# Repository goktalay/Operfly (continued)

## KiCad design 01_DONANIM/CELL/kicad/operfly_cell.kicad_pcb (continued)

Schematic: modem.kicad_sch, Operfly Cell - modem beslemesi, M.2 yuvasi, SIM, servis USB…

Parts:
C24, C25: 10u 50V; C_1206_3216Metric
C26: 100n 50V; C_0603_1608Metric
C27: 15n; C_0402_1005Metric
C28, C38, C39: 220p; C_0402_1005Metric
C29: 100n 25V; C_0603_1608Metric
C30, C31: 47u 16V; C_1210_3225Metric
C32, C35, C36, C45, C49, C53, C54: 100n; C_0402_1005Metric
C33, C34: 220u 6V3 polimer; CP_EIA-7343-31_Kemet-D
C37: 6n8; C_0402_1005Metric
C40, C41: 68p; C_0402_1005Metric
C42: 15p; C_0402_1005Metric
C43: 9p1; C_0402_1005Metric
C44: 4p7; C_0402_1005Metric
C46, C47, C48, C50, C51, C52: 10p; C_0402_1005Metric
C55: 1u 25V; C_0603_1608Metric
D6: PDS760 (60 V, 7 A); D_PowerDI-5
D7: SMAJ5.0A; D_SMA
D8: LED mavi (radyo acik); LED_0603_1608Metric
D9, D10: TPD4E05U06DQA; USON-10_2.5x1.0mm_P0.5mm
D11: USBLC6-2P6; SOT-666
J2: M.2 Key B (5G modem, 3052); TE_M.2_B_2x38-1MP_P0.5mm
J3: nano-SIM 1; nanoSIM_GCT_SIM8060-6-0-14-00
J4: nano-SIM 2; nanoSIM_GCT_SIM8060-6-0-14-00
J5: USB Type-C (servis); USB_C_Receptacle_GCT_USB4105-xx-A_16P_TopMnt_Horizontal
L2: 10u XAL7070-103; L_Coilcraft_XAL7070-XXX
Q1, Q2: 2N7002; SOT-23
R13: 294k 1%; R_0402_1005Metric
R14: 43k2 1%; R_0402_1005Metric
R15: 243k 1%; R_0402_1005Metric
R16: 26k7; R_0402_1005Metric
R17: 38k3 1%; R_0402_1005Metric
R18: 10k2 1%; R_0402_1005Metric
R19, R20: 10k 1%; R_0402_1005Metric
R21, R22, R23, R43, R44: 100k; R_0402_1005Metric
R24, R25: 10k; R_0402_1005Metric
R26: 330R; R_0402_1005Metric
R27, R28, R29, R31, R32, R33: 22R; R_0402_1005Metric
R30, R34: 15k; R_0402_1005Metric
R35, R36, R37, R38, R39, R40: 0R; R_0402_1005Metric
R41, R42: 15k DNP; R_0402_1005Metric; not fitted
R45, R46: 5k1 1%; R_0402_1005Metric
TP4: +3V8_MODEM; TestPoint_Pad_D1.0mm
TP5: MODEM_RESET_N; TestPoint_Pad_D1.0mm
TP6: MODEM_ON; TestPoint_Pad_D1.0mm
U7: TPS54560BDDAR; Texas_R-PDSO-G8_EP2.95x4.9mm_Mask2.4x3.1mm_ThermalVias
U8: FSUSB42MUX; MSOP-10_3x3mm_P0.5mm

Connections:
+3V3: C53.1, R24.1, R25.1, U8.1 (VCC); also elsewhere on the board
+3V8_MODEM: C30.1, C31.1, C33.1, C34.1, C35.1, C36.1, C37.1, C38.1, C39.1, C40.1, C41.1, C42.1, C43.1, C44.1, D7.1 (A1), J2.2 (3.3V), J2.4 (3.3V), J2.70 (3.3V), J2.72 (3.3V), J2.74 (3.3V), L2.2, R17.1, R19.1, R26.1, TP4.1; also elsewhere on the board
+12V: C24.1, C25.1, C26.1, R13.1, U7.2 (VIN); also elsewhere on the board
GND: C24.2, C25.2, C26.2, C27.2, C28.2, C30.2, C31.2, C32.2, C33.2, C34.2, C35.2, C36.2, C37.2, C38.2, C39.2, C40.2, C41.2, C42.2, C43.2, C44.2, C45.2, C46.2, C47.2, C48.2, C49.2, C50.2, C51.2, C52.2, C53.2, C54.2, C55.2, D6.2 (A), D7.2 (A2), D9.3 (GND), D9.8 (GND), D10.3 (GND), D10.8 (GND), D11.2 (GND), J2.3 (GND), J2.5 (GND), J2.11 (GND), J2.27 (GND), J2.33 (GND), J2.39 (GND), J2.45 (GND), J2.51 (GND), J2.57 (GND), J2.71 (GND), J2.73 (GND), J3.5 (GND), J3.SH, J4.5 (GND), J4.SH, J5.A1 (GND), J5.A12 (GND), J5.B1 (GND), J5.B12 (GND), J5.SH (SHIELD), Q1.2 (S), Q2.2 (S), R14.2, R15.2, R18.2, R20.2, R21.2, R22.2, R23.2, R41.2, R42.2, R44.2, R45.2, R46.2, U7.7 (GND), U7.9 (GND), U8.5 (GND), U8.10 (~OE); also elsewhere on the board
MCU_USB_DM: R42.1, U8.6 (HSD1-); also elsewhere on the board
MCU_USB_DP: R41.1, U8.7 (HSD1+); also elsewhere on the board
MDM_BOOT: C29.1, U7.1 (BOOT)
MDM_COMP: C28.1, R16.1, U7.6 (COMP)
MDM_COMP_RC: C27.1, R16.2
MDM_EN: Q1.3 (D), R13.2, R14.1, U7.3 (EN)
MDM_FB: R17.2, R18.1, U7.5 (FB)
MDM_RT: R15.1, U7.4 (RT/CLK)
MDM_SW: C29.2, D6.1 (K), L2.1, U7.8 (SW)
MODEM_LED_A: D8.2 (A), R26.2
MODEM_LED_N: D8.1 (K), J2.10 (GPIO_9/DAS/~DSS/~LED1)
MODEM_ON: J2.6 (~FULL_CARD_POWER_OFF), R23.1, TP6.1; also elsewhere on the board
MODEM_PWR_OFF: Q1.1 (G), R21.1; also elsewhere on the board
MODEM_RESET_N: J2.67 (~RESET), Q2.3 (D), TP5.1
MODEM_RF_EN: J2.8 (~W_DISABLE1), R24.2; also elsewhere on the board
MODEM_RST: Q2.1 (G), R22.1; also elsewhere on the board
MODEM_USB_DM: R40.2, U8.4 (D-)
MODEM_USB_DM_M: J2.9 (USB_D-), R40.1
MODEM_USB_DP: R39.2, U8.3 (D+)
MODEM_USB_DP_M: J2.7 (USB_D+), R39.1
MODEM_VSENS: C32.1, R19.2, R20.1; also elsewhere on the board
MODEM_WAKE_N: J2.23 (GPIO_11), R25.2; also elsewhere on the board
PCIE_CLKREQ_N: J2.52 (~CLKREQ); also elsewhere on the board
PCIE_CLK_N: J2.53 (REFCLKn); also elsewhere on the board
PCIE_CLK_P: J2.55 (REFCLKp); also elsewhere on the board
PCIE_MRX_N: J2.47 (PETn0/SATA-A-); also elsewhere on the board
PCIE_MRX_P: J2.49 (PETp0/SATA-A+); also elsewhere on the board
PCIE_MTX_N: J2.41 (PERn0/SATA-B+); also elsewhere on the board
PCIE_MTX_P: J2.43 (PERp0/SATA-B-); also elsewhere on the board
PCIE_RST_N: J2.50 (~PERST); also elsewhere on the board
PCIE_WAKE_N: J2.54 (~PEWAKE); also elsewhere on the board
SVC_USB_DM: D11.3 (I/O2), D11.4 (I/O2), J5.A7 (D-), J5.B7 (D-), U8.8 (HSD2-)
SVC_USB_DP: D11.1 (I/O1), D11.6 (I/O1), J5.A6 (D+), J5.B6 (D+), U8.9 (HSD2+)
USB_CC1: J5.A5 (CC1), R45.1
USB_CC2: J5.B5 (CC2), R46.1
USB_SEL: C54.1, R43.2, R44.1, U8.2 (SEL); also elsewhere on the board
USB_VBUS: C55.1, D11.5 (VBUS), J5.A4 (VBUS), J5.A9 (VBUS), J5.B4 (VBUS), J5.B9 (VBUS), R43.1
USIM1_CLK: J2.32 (UIM-CLK), R28.1
USIM1_CLK_K: C47.1, D9.4 (D2+), J3.3 (CLK), R28.2
USIM1_DATA: J2.34 (UIM-DATA), R29.1
USIM1_DATA_K: C48.1, D9.5 (D2-), J3.7 (I/O), R29.2, R30.2
USIM1_RST: J2.30 (UIM-RESET), R27.1
USIM1_RST_K: C46.1, D9.2 (D1-), J3.2 (RST), R27.2
USIM1_VDD: C45.1, D9.1 (D1+), J2.36 (UIM-PWR), J3.1 (VCC), R30.1
USIM2_CLK: R32.1, R37.2
USIM2_CLK_K: C51.1, D10.4 (D2+), J4.3 (CLK), R32.2
USIM2_CLK_M: J2.44 (GPIO_2), R37.1
USIM2_DATA: R33.1, R38.2
USIM2_DATA_K: C52.1, D10.5 (D2-), J4.7 (I/O), R33.2, R34.2
USIM2_DATA_M: J2.42 (GPIO_1), R38.1
USIM2_RST: R31.1, R36.2
USIM2_RST_K: C50.1, D10.2 (D1-), J4.2 (RST), R31.2
USIM2_RST_M: J2.46 (GPIO_3), R36.1
USIM2_VDD: C49.1, D10.1 (D1+), J4.1 (VCC), R34.1, R35.2
USIM2_VDD_M: J2.48 (GPIO_4), R35.1

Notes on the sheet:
koruma dizisi (uretici onerisi). Kart algilama kullanilmaz (ucusta sicak takma yok). Ikinci yuva ileride lehimli eSIM ile degisebilir.
KURAL: besleme, modem FULL_CARD_POWER_OFF# ile kapatilip 1 s beklenmeden KESILMEZ (modemin dahili bellegi bozulabilir).
Cikis 3,80 V (38k3 / 10k2). Giris 9,0 V'ta acar, 8,0 V'ta kapatir (294k / 43k2). Varsayilan ACIK; islemci MODEM_PWR_OFF ile kapatir.
41/43 modemin PCIe VERICISI, 47/49 modemin PCIe ALICISI. Modem kok (RC) kipinde: PCIE_RST_N ve saat modemden cikar.
VCC yaninda: 2 x 220 uF dusuk ESR + seramik dizi + 5 V kirpma diyodu (uretici onerisi). Bos birakilan uclar kilavuza gore bos kalir.
MODEM BESLEMESI (TPS54560B, 400 kHz): omurga 12 V'undan 3,8 V / 5 A. Modem 3,135-4,4 V ister, verici patlamalarinda 3 A ceker.
Servis USB'si karti BESLEMEZ; modem ayarlanirken ya da guncellenirken kart omurgadan beslenmelidir.
kablo takili degilken dugum islemcisine (USB ana bilgisayar, AT komutlari), servis USB'sine kablo takilinca (VBUS gelince) bilgisayara.
MODEM USB'si (USB 2.0): AT komutlari ve modem yazilimi guncellemesi yalnizca buradan yapilir. Anahtar (FSUSB42) hatti iki yere verir:
MODEM YUVASI (M.2 Key B, 3052): uc numaralari modem kilavuzundaki gibidir. Yuva sembolundeki adlar bilgisayar tarafina goredir:
SIM KARTLAR (2 x nano-SIM, cift operator, ayni anda biri etkin): 22R seri, 10 pF, veri hattinda 15k yukari cekme, dusuk sigali

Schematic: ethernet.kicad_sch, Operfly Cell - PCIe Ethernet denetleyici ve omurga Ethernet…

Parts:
C56: 10u 25V; C_1206_3216Metric
C57: 100n 25V; C_0603_1608Metric
C58, C59: 22u 10V; C_1206_3216Metric
C60: 3n3; C_0402_1005Metric
C61, C62: 220n; C_0402_1005Metric
C63, C64: 27p; C_0402_1005Metric
C65, C66, C67, C69, C70, C71, C72, C74, C75, C76, C77: 100n; C_0402_1005Metric
C68, C73: 4u7; C_0603_1608Metric
C78: 1n 2kV; C_1206_3216Metric
D12: LED yesil (Ethernet); LED_0603_1608Metric
D13: LED sari (Ethernet); LED_0603_1608Metric
L3: 2u2 XAL4020-222; L_Coilcraft_XAL4020-XXX
R47: 316k 1%; R_0402_1005Metric
R48: 100k 1%; R_0402_1005Metric
R49: 100k; R_0402_1005Metric
R50: 4k7; R_0402_1005Metric
R51, R52: 10k; R_0402_1005Metric
R53: 1k; R_0402_1005Metric
R54: 15k; R_0402_1005Metric
R55: 2k49 1%; R_0402_1005Metric
R56, R57: 510R; R_0402_1005Metric
R58, R59, R60, R61: 75R; R_0402_1005Metric
T1: TG111-MSC13LF; Transformer_Ethernet_HALO_TG111-MSC13
TP7: +3V3_ETH; TestPoint_Pad_D1.0mm
U9: TPS62130RGTR; VQFN-16-1EP_3x3mm_P0.5mm_EP1.68x1.68mm_ThermalVias
U10: RTL8111H-CG; QFN-32-1EP_4x4mm_P0.4mm_EP2.9x2.9mm_ThermalVias
Y2: 25 MHz 30 ppm; Crystal_SMD_3225-4Pin_3.2x2.5mm

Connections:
+3V3: R49.1; also elsewhere on the board
+3V3_ETH: C58.1, C59.1, C65.1, C66.1, C67.1, C68.1, L3.2, R47.1, R50.1, R51.1, R52.1, R53.1, R56.1, R57.1, TP7.1, U9.14 (VOS), U10.11 (AVDD33), U10.23 (VDDREG), U10.32 (AVDD33)
+3V8_MODEM: U9.13 (EN); also elsewhere on the board
+5V: C56.1, C57.1, U9.10 (VIN), U9.11 (VIN), U9.12 (VIN); also elsewhere on the board
ETH_1V0: C69.1, C70.1, C71.1, C72.1, C73.1, U10.3 (AVDD10), U10.8 (AVDD10), U10.22 (DVDD10), U10.24 (REGOUT), U10.30 (AVDD10)
ETH_A+: T1.23 (MTX1+); also elsewhere on the board
ETH_A-: T1.22 (MTX1-); also elsewhere on the board
ETH_B+: T1.20 (MTX2+); also elsewhere on the board
ETH_B-: T1.19 (MTX2-); also elsewhere on the board
ETH_BS: C78.1, R58.2, R59.2, R60.2, R61.2
ETH_C+: T1.17 (MTX3+); also elsewhere on the board
ETH_C-: T1.16 (MTX3-); also elsewhere on the board
ETH_CT_A: C74.1, T1.1 (TCT1)
ETH_CT_B: C75.1, T1.4 (TCT2)
ETH_CT_C: C76.1, T1.7 (TCT3)
ETH_CT_D: C77.1, T1.10 (TCT4)
ETH_D+: T1.14 (MX4+); also elsewhere on the board
ETH_D-: T1.13 (MX4-); also elsewhere on the board
ETH_ISOLATE_N: R53.2, R54.1, U10.20 (ISOLATEB)
ETH_KCT_A: R58.1, T1.24 (MTC1)
ETH_KCT_B: R59.1, T1.21 (MCT2)
ETH_KCT_C: R60.1, T1.18 (MCT3)
ETH_KCT_D: R61.1, T1.15 (MCT4)
ETH_LED0: D12.1 (K), U10.27 (LED0)
ETH_LED0_A: D12.2 (A), R56.2
ETH_LED2: D13.1 (K), U10.25 (LED2)
ETH_LED2_A: D13.2 (A), R57.2
ETH_MDI0_N: T1.3 (TD1-), U10.2 (MDIN0)
ETH_MDI0_P: T1.2 (TD1+), U10.1 (MDIP0)
ETH_MDI1_N: T1.6 (TD2-), U10.5 (MDIN1)
ETH_MDI1_P: T1.5 (TD2+), U10.4 (MDIP1)
ETH_MDI2_N: T1.9 (TD3-), U10.7 (MDIN2)
ETH_MDI2_P: T1.8 (TD3+), U10.6 (MDIP2)
ETH_MDI3_N: T1.12 (TD4-), U10.10 (MDIN3)
ETH_MDI3_P: T1.11 (TD4+), U10.9 (MDIP3)
ETH_PG: R49.2, U9.4 (PG); also elsewhere on the board
ETH_RSET: R55.1, U10.31 (RSET)
ETH_TX_N: C62.1, U10.18 (HSON)
ETH_TX_P: C61.1, U10.17 (HSOP)
ETH_XI: C63.1, U10.28 (CKXTAL1), Y2.1
ETH_XO: C64.1, U10.29 (CKXTAL2), Y2.3
GND: C56.2, C57.2, C58.2, C59.2, C60.2, C63.2, C64.2, C65.2, C66.2, C67.2, C68.2, C69.2, C70.2, C71.2, C72.2, C73.2, C74.2, C75.2, C76.2, C77.2, C78.2, R48.2, R54.2, R55.2, U9.6 (GND), U9.7 (FSW), U9.8 (DEF), U9.15 (GND), U9.16 (GND), U9.17 (GND), U10.33 (GND), Y2.2 (G), Y2.4 (G); also elsewhere on the board
PCIE_CLKREQ_N: R51.2, U10.12 (CLKREQB); also elsewhere on the board
PCIE_CLK_N: U10.16 (REFCLK_N); also elsewhere on the board
PCIE_CLK_P: U10.15 (REFCLK_P); also elsewhere on the board
PCIE_MRX_N: C62.2; also elsewhere on the board
PCIE_MRX_P: C61.2; also elsewhere on the board
PCIE_MTX_N: U10.14 (HSIN); also elsewhere on the board
PCIE_MTX_P: U10.13 (HSIP); also elsewhere on the board
PCIE_RST_N: R50.2, U10.19 (PERSTB); also elsewhere on the board
PCIE_WAKE_N: R52.2, U10.21 (LANWAKEB); also elsewhere on the board
REG33E_FB: R47.2, R48.1, U9.5 (FB)
REG33E_SS: C60.1, U9.9 (SS/TR)
REG33E_SW: L3.1, U9.1 (SW), U9.2 (SW), U9.3 (SW)

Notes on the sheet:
kablo tarafi 75R -> 1 nF 2 kV (Vision ve Hub ile ayni).
Modemin vericisi (41/43) dogrudan HSIP/HSIN'e gelir (kondansator modemin icinde); denetleyicinin vericisi 220 nF ile modemin alicisina gider.
ve PCIe yukari cekme direncleri de gerilimsiz kalir (kapali modemin uclarina gerilim verilmez).
PCIE_RST_N kok kipinde modemin acik savak cikisidir: 4k7 yukari cekme. Cevre degerleri (RSET, 1,0 V kondansatorleri, ISOLATEB) README'de 'dogrulanacak'.
PCIe ETHERNET DENETLEYICI (RTL8111H-CG, 1 Gbit): modem PCIe kok aygitidir, bu entegreyi kendisi surer (modemde AT komutuyla acilir).
3,3 V (TPS62130, 5 V'tan): yalnizca Ethernet denetleyici icin. Modem beslemesi gelince acar; modem beslemesi yokken denetleyici
TRAFO (TG111-MSC13LF) ve OMURGA ETHERNET'i: dort cift omurga fisine gider (Hub'in anahtarina). Orta uclar: entegre tarafi 100n -> GND,

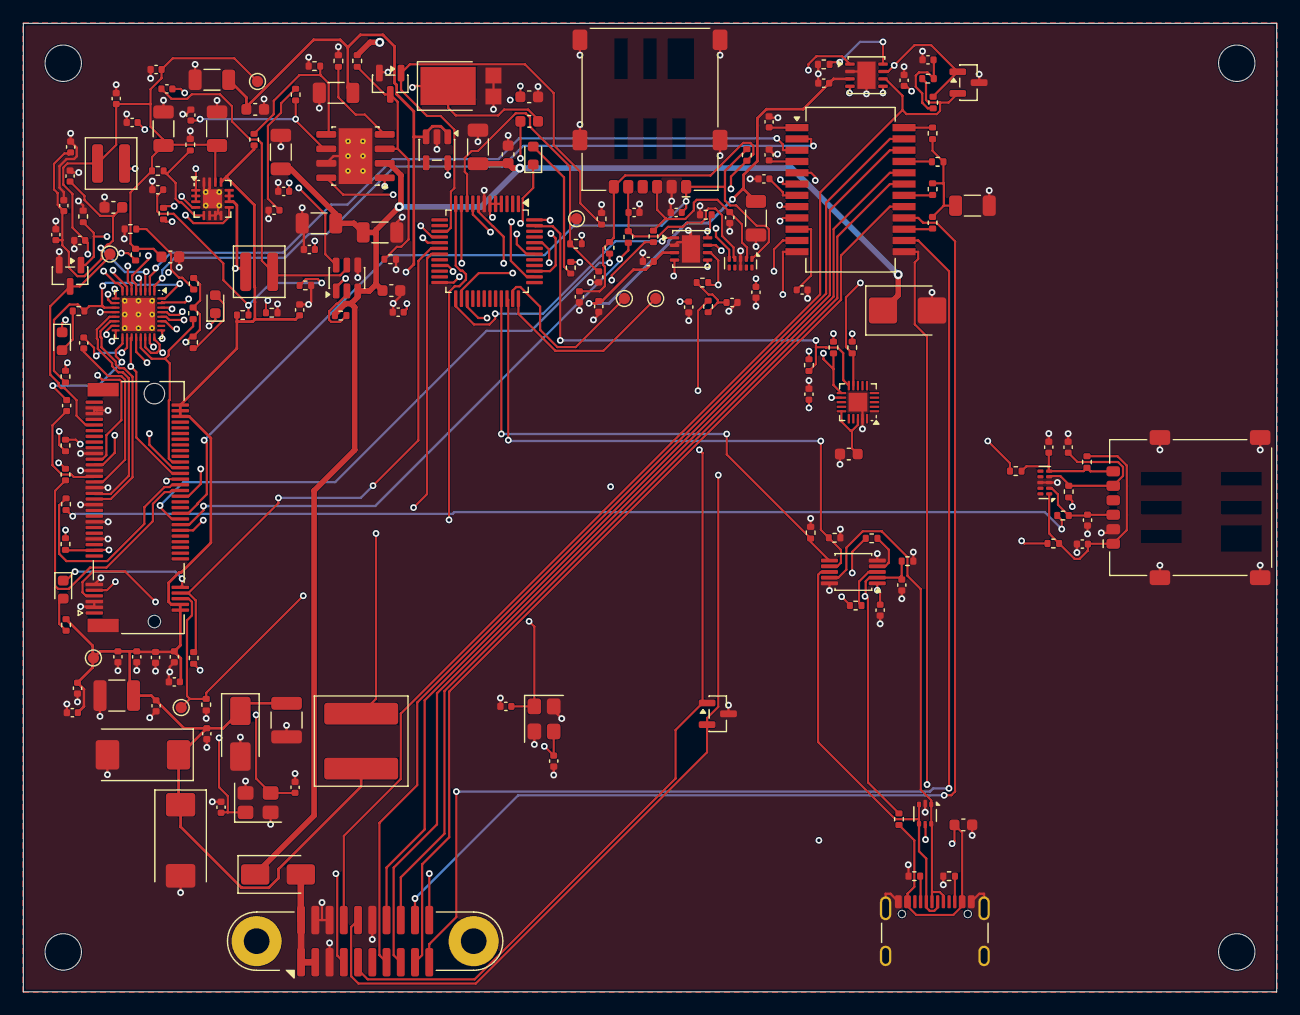
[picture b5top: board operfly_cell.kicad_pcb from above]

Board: 6 copper layers, 110.0 x 85.0 mm, 186 parts (0 on the bottom side), 128 nets.

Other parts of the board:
H1, H2, H3, H4: M3; MountingHole_3.2mm_M3

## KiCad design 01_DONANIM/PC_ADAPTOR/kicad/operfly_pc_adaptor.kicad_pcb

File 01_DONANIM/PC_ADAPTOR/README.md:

# Operfly PC adaptörü (OPFPCA)

Bilgisayarı omurgaya bağlar: USB Type-C tarafında gigabit Ethernet ve CAN FD; kendisi de sertifikalı bir Operfly kartıdır.

## Durum (15 Kasım 2026)

- KiCad projesi: `kicad/operfly_pc_adaptor.kicad_pro`.
  Üretim ve denetim: `python 10_ORTAK_ARACLAR/kicad/denetle.py PC_ADAPTOR operfly_pc_adaptor`.
- Şematik tamam, 4 sayfa: düğüm (`dugum`), USB/göbek/beslemeler (`usb`), Ethernet köprüsü (`ethernet`).
  ERC 0 hata, 0 uyarı. Kart çizimi başlamadı.

## Kararlar (sahibi kararı tasarımcıya bıraktı)

1. **Tek USB Type-C kablosu, içeride USB göbeği** (USB2514B). 1. portunda Ethernet köprüsü, 2. portunda düğüm
   işlemcisinin USB'si (CAN FD geçidi ve kimlik doğrulama) var. Bilgisayar iki aygıt görür; tek kablo yeter.
2. **Ethernet köprüsü LAN7500i** (USB 2.0 yüksek hız, gigabit Ethernet). Bağlantıları üreticinin şematik denetim
   listesine göre yapıldı. USB 2.0 hattı gerçek veri hızını yaklaşık 300-400 Mbit/s ile sınırlar; yapılandırma,
   kayıt indirme ve canlı izleme için yeterlidir. USB 3 köprüsü sonraki revizyon seçeneğidir.
3. **Kart USB'den beslenir, omurgaya 12 V vermez.** Bağlandığı kart kendi beslemesini taşır. Tahmini tüketim 2 W
   civarı (5 V'ta yaklaşık 0,4 A); standart USB 2.0 portunun 0,5 A sınırına yakındır, bu yüzden Type-C ya da
   USB 3 portu önerilir.
4. **Beslemeler:** 5 V'tan 3,3 V ve 1,2 V (iki TPS62130). Köprünün içinde regülatör yoktur.
5. **CAN sonlandırması 120 ohm dizili.** Adaptör tek karta doğrudan bağlandığında hat bu dirençle sonlanır.
   Hub'a bağlandığında toplam yük yaklaşık 40 ohm olur (sınırda; ölçülecek, gerekirse direnç sökülür).
6. **Köprünün MAC adresi için EEPROM yok;** adres yazılımdan verilir. Şartname gereği dış ağa çıkan üründe resmi
   adres bloğu gerekir; kalıcı adres için EEPROM sonraki revizyonda eklenecek.
7. **Sıfırlama:** 3,3 V yaklaşık 3,0 V'u geçene kadar göbek ve köprü sıfırda tutulur.
8. **Göbeğin kullanılmayan 3. ve 4. portları kapalı** (üreticinin önerdiği 10 k yukarı çekmelerle).

## Doğrulanacaklar

- USB2514B ayar kayışları (veri yolundan beslenen çalışma, 1. ve 2. portların çıkarılamaz işaretlenmesi) üretici
  belgesindeki tabloyla karşılaştırılacak.
- LAN7500i: kullanılmayan JTAG, GPIO ve EEPROM uçlarının bağlanma önerisi; kristal yük kondansatörleri (15-33 pF aralığı).
- TPS62130 ve TPS3808 ayrıntıları (Hub ve Core doğrulama listeleriyle ortak).
- Toplam USB akımı ölçülecek.

## Kart çizimi (otomatik)

Sahibinin kararıyla kart **otomatik** çizildi: yerleşim `pcb_yerlesim.py`, yollar dış bir otomatik yol çiziciyle
(`pcb_ciz.py`). Dosya: `kicad/operfly_pc_adaptor.kicad_pcb`; ayarlar `kicad/pcb_ayar.py`.
Yeniden üretmek için: `python 10_ORTAK_ARACLAR/kicad/pcb_ciz.py PC_ADAPTOR operfly_pc_adaptor`.

- **Kart:** 80 x 55 mm, 4 katman (üst: elemanlar + sinyal, iç 1: toprak, iç 2: +3V3, alt: sinyal), 140 eleman, tamamı üst yüzde; köşelerde M3 montaj deliği.
- **Kurallar:** yol 0,20 mm, açıklık 0,125 mm, geçiş 0,6/0,3 mm; besleme ağları, ağın en dar ucunu aşmayacak biçimde 0,2-1,0 mm (0,4 mm ve üstünde geçiş 0,8/0,4 mm); bakır-kenar 0,25 mm.
- **Denetim:** DRC 0 ihlal, 0 bağlanmamış uç; şematik-kart uyumu temiz. 1157 yol parçası, 218 geçiş.

**Bu bir mühendis çizimi değildir.** Üretimden önce bir kart tasarımcısının bakması gereken noktalar:

- USB 2.0 çiftleri (Type-C → göbek → Ethernet denetleyicisi ve işlemci) ile gigabit Ethernet çiftleri 90/100 ohm fark empedansında ve eşit uzunlukta çizilmedi; bağlantı kurulsa bile hız düşebilir ya da hata verebilir.
- Ethernet denetleyicisinin (LAN7500i) 1,2 V çeviricisi, kristalleri ve trafo çevresi üretici yerleşim önerisine göre düzenlenmedi.
- Anahtarlamalı regülatörlerin (bobin, diyot, giriş/çıkış kondansatörleri) akım döngüleri küçük tutulmadı; gürültü ve verim ölçülmeli.
- Kristal ve osilatör hatları en kısa yoldan çizilmedi; altlarından başka sinyal geçip geçmediğine bakılmalı.
- Fark çiftleri (CAN, USB, Ethernet) çift olarak, eşit uzunlukta ve empedans denetimli çizilmedi.
- Güç elemanlarının soğutma bakırı ve ısıl geçişleri ayrıca hesaplanmadı.
- Eleman adları üretim katmanında bırakıldı; kart üstünde yazı (serigrafi) yok.
- Kasa, konnektör yerleri ve montaj delikleri mekanik tasarımla eşleştirilmedi.
- Üretim dosyaları (Gerber, delik, dizgi) henüz çıkarılmadı.

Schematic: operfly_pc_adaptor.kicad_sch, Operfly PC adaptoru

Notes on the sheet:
Operfly PC adaptoru (OPFPCA)
Sematik betikle uretilir: 01_DONANIM/PC_ADAPTOR/kicad/uret.py

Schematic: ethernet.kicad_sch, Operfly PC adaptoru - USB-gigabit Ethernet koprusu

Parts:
C40, C41: 18p; C_0402_1005Metric
C42, C43, C44, C45, C46, C47, C48, C49, C50, C51, C52, C53, C54, C55, C56, C57, C58, C59: 10n; C_0402_1005Metric
C60, C61, C62, C63, C64, C65: 10u; C_0805_2012Metric
C66: 1n 2kV; C_1206_3216Metric
FB2, FB3, FB4, FB5: BLM18PG221; L_0603_1608Metric
R31: 8k06 1%; R_0402_1005Metric
R32: 12k 1%; R_0402_1005Metric
R33, R34, R35, R36, R37, R38, R39, R40: 49R9 1%; R_0402_1005Metric
R41, R42, R43, R44: 75R; R_0402_1005Metric
T1: TG111-MSC13LF; Transformer_Ethernet_HALO_TG111-MSC13
U9: LAN7500i-ABZJ; QFN-56-1EP_8x8mm_P0.5mm_EP5.9x5.9mm
Y3: 25 MHz; Crystal_SMD_3225-4Pin_3.2x2.5mm

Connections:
+1V2: C46.1, C47.1, C48.1, C49.1, C50.1, C51.1, C52.1, C61.1, FB3.1, FB4.1, FB5.1, U9.8 (VDD12CORE), U9.11 (VDD12CORE), U9.20 (VDD12CORE), U9.23 (VDD12CORE), U9.30 (VDD12CORE), U9.36 (VDD12CORE), U9.49 (VDD12BIAS); also elsewhere on the board
+3V3: C42.1, C43.1, C44.1, C45.1, C60.1, FB2.1, R33.1, R34.1, R35.1, R36.1, R37.1, R38.1, R39.1, R40.1, T1.1 (TCT1), T1.4 (TCT2), T1.7 (TCT3), T1.10 (TCT4), U9.7 (VDDVARIO), U9.19 (VDDVARIO), U9.24 (VDDVARIO), U9.37 (VDDVARIO); also elsewhere on the board
ETH_A+: T1.23 (MTX1+); also elsewhere on the board
ETH_A-: T1.22 (MTX1-); also elsewhere on the board
ETH_B+: T1.20 (MTX2+); also elsewhere on the board
ETH_B-: T1.19 (MTX2-); also elsewhere on the board
ETH_BS: C66.1, R41.2, R42.2, R43.2, R44.2
ETH_C+: T1.17 (MTX3+); also elsewhere on the board
ETH_C-: T1.16 (MTX3-); also elsewhere on the board
ETH_D+: T1.14 (MX4+); also elsewhere on the board
ETH_D-: T1.13 (MX4-); also elsewhere on the board
ETH_RBIAS: R31.1, U9.41 (ETHRBIAS)
ETH_USBRBIAS: R32.1, U9.16 (USBRBIAS)
ETH_VDD12A: C54.1, C55.1, C56.1, C57.1, C63.1, FB3.2, U9.45 (VDD12A), U9.48 (VDD12A), U9.53 (VDD12A), U9.56 (VDD12A)
ETH_VDD12PLL: C59.1, C65.1, FB5.2, U9.50 (VDD12PLL)
ETH_VDD12USB: C58.1, C64.1, FB4.2, U9.17 (VDD12USBPLL)
ETH_VDD33A: C53.1, C62.1, FB2.2, U9.14 (VBUS_DET), U9.15 (VDD33A)
ETH_XI: C40.1, U9.5 (XI), Y3.1
ETH_XO: C41.1, U9.6 (XO), Y3.3
GND: C40.2, C41.2, C42.2, C43.2, C44.2, C45.2, C46.2, C47.2, C48.2, C49.2, C50.2, C51.2, C52.2, C53.2, C54.2, C55.2, C56.2, C57.2, C58.2, C59.2, C60.2, C61.2, C62.2, C63.2, C64.2, C65.2, C66.2, R31.2, R32.2, U9.39 (TEST), U9.57 (GND), Y3.2 (G), Y3.4 (G); also elsewhere on the board
KCT_A: R41.1, T1.24 (MTC1)
KCT_B: R42.1, T1.21 (MCT2)
KCT_C: R43.1, T1.18 (MCT3)
KCT_D: R44.1, T1.15 (MCT4)
MDI_A+: R33.2, T1.2 (TD1+), U9.44 (TR0P)
MDI_A-: R34.2, T1.3 (TD1-), U9.43 (TR0N)
MDI_B+: R35.2, T1.5 (TD2+), U9.47 (TR1P)
MDI_B-: R36.2, T1.6 (TD2-), U9.46 (TR1N)
MDI_C+: R37.2, T1.8 (TD3+), U9.52 (TR2P)
MDI_C-: R38.2, T1.9 (TD3-), U9.51 (TR2N)
MDI_D+: R39.2, T1.11 (TD4+), U9.55 (TR3P)
MDI_D-: R40.2, T1.12 (TD4-), U9.54 (TR3N)
USB1_DM: U9.12 (USBDM); also elsewhere on the board
USB1_DP: U9.13 (USBDP); also elsewhere on the board
USB_RESET_N: U9.42 (~RESET); also elsewhere on the board

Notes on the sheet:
ETHERNET KOPRUSU (LAN7500i, 25 MHz): baglantilar ureticinin sematik denetim listesine gore. Icinde regulator yok; tum beslemeler dis.
HAT: her uca 49,9 ohm yukari cekme (3,3 V); trafonun entegre tarafi orta uclari ayni 3,3 V'a; kablo tarafi 75 ohm + 1 nF.
EEPROM yok: MAC adresi yazilimdan verilir (kalici adres icin EEPROM sonraki revizyonda). JTAG ve GPIO uclari bos.

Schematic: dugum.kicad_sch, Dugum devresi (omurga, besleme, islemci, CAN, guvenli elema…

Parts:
C1: 4u7; C_0603_1608Metric
C2, C3, C4, C7, C8, C9, C11, C12, C14: 100n; C_0402_1005Metric
C5, C6: 10p; C_0402_1005Metric
C10, C13: 4n7; C_0402_1005Metric
C15: 2u2; C_0603_1608Metric
D1: LED yesil; LED_0603_1608Metric
D2, D3: NUP2105L; SOT-23
J1: Operfly Bus; Harwin_Gecko_G125-MS12005M2P_2x10_P1.25mm_Vertical
R1, R3, R6, R11: 10k; R_0402_1005Metric
R2: 1k; R_0402_1005Metric
R4, R5, R7, R8: 60R4; R_0402_1005Metric
R9, R10: 2k2; R_0402_1005Metric
TP1: SWDIO; TestPoint_Pad_D1.0mm
TP2: SWCLK; TestPoint_Pad_D1.0mm
TP3: NRST; TestPoint_Pad_D1.0mm
U1: STM32G0B1CET6; LQFP-48_7x7mm_P0.5mm
U2, U3: TJA1051TK/3; HVSON-8-1EP_3x3mm_P0.65mm_EP1.6x2.4mm
U4: SE050E2HQ1; QFN-20-1EP_3x3mm_P0.4mm_EP1.65x1.65mm
Y1: 16 MHz; Crystal_SMD_3225-4Pin_3.2x2.5mm

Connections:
+3V3: C1.1, C2.1, C3.1, C4.1, C9.1, C12.1, C14.1, R1.1, R2.1, R9.1, R10.1, R11.1, U1.4 (VBAT), U1.5 (VREF+), U1.6 (VDD), U2.5 (VIO), U3.5 (VIO), U4.12 (VIN); also elsewhere on the board
+5V: C8.1, C11.1, U2.3 (VCC), U3.3 (VCC); also elsewhere on the board
CAN_A_H: D2.1 (K), J1.4 (CAN_A_H), R4.1, U2.7 (CANH)
CAN_A_L: D2.2 (K), J1.14 (CAN_A_L), R5.1, U2.6 (CANL)
CAN_A_RX: U1.38 (PD0), U2.4 (RXD)
CAN_A_S: R3.1, U1.27 (PB15), U2.8 (S)
CAN_A_TERM: C10.1, R4.2, R5.2
CAN_A_TX: U1.39 (PD1), U2.1 (TXD)
CAN_B_H: D3.1 (K), J1.5 (CAN_B_H), R7.1, U3.7 (CANH)
CAN_B_L: D3.2 (K), J1.15 (CAN_B_L), R8.1, U3.6 (CANL)
CAN_B_RX: U1.24 (PB12), U3.4 (RXD)
CAN_B_S: R6.1, U1.21 (PB2), U3.8 (S)
CAN_B_TERM: C13.1, R7.2, R8.2
CAN_B_TX: U1.25 (PB13), U3.1 (TXD)
ETH_A+: J1.7 (ETH_A+); also elsewhere on the board
ETH_A-: J1.17 (ETH_A-); also elsewhere on the board
ETH_B+: J1.8 (ETH_B+); also elsewhere on the board
ETH_B-: J1.18 (ETH_B-); also elsewhere on the board
ETH_C+: J1.9 (ETH_C+); also elsewhere on the board
ETH_C-: J1.19 (ETH_C-); also elsewhere on the board
ETH_D+: J1.10 (ETH_D+); also elsewhere on the board
ETH_D-: J1.20 (ETH_D-); also elsewhere on the board
GND: C1.2, C2.2, C3.2, C4.2, C5.2, C6.2, C7.2, C8.2, C9.2, C10.2, C11.2, C12.2, C13.2, C14.2, C15.2, D2.3 (A), D3.3 (A), J1.3 (GND), J1.12 (GND), J1.13 (GND), J1.16 (GND), R3.2, R6.2, U1.7 (VSS), U2.2 (GND), U2.9 (GND), U3.2 (GND), U3.9 (GND), U4.19 (VSS), U4.21 (EP), Y1.2 (G), Y1.4 (G); also elsewhere on the board
HSE_IN: C5.1, U1.8 (PF0), Y1.1
HSE_OUT: C6.1, U1.9 (PF1), Y1.3
LED_DURUM: D1.1 (K), U1.26 (PB14)
LED_DURUM_A: D1.2 (A), R2.2
NRST: C7.1, R1.2, TP3.1, U1.10 (PF2)
SE_ENA: R11.2, U1.44 (PB5), U4.11 (ENA)
SE_SCL: R9.2, U1.47 (PB8), U4.10 (I2C_SCL)
SE_SDA: R10.2, U1.48 (PB9), U4.9 (I2C_SDA)
SE_VCC: C15.1, U4.15 (VOUT), U4.18 (VCC)
SWCLK: TP2.1, U1.36 (PA14)
SWDIO: TP1.1, U1.35 (PA13)
USB2_DM: U1.33 (PA9/PA11); also elsewhere on the board
USB2_DP: U1.34 (PA10/PA12); also elsewhere on the board

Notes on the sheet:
OMURGA PORTU ve GIRIS KORUMASI: ters baglanti diyotu, 18 V kirpma diyotu. +12V korumali omurga gerilimidir.
DUGUM ISLEMCISI (STM32G0B1CET6): omurgaya iki CAN FD hattiyla baglanir, kimligini guvenli elemanla kanitlar.
CAN FD: iki bagimsiz alici-verici (TJA1051-3). Sessiz mod girisi asagi cekili. Sonlandirma Hub'dadir; yerleri hazir, dizilmez.
GUVENLI ELEMAN (SE050): kart kimligi ve sertifikasi. SE_ENA sifira cekilince eleman kapanir (sifirlama).

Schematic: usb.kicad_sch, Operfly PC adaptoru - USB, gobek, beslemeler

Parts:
C16: 4u7 16V; C_0805_2012Metric
C17, C19, C24, C28, C31, C32, C33, C34, C35, C36, C37, C38: 100n; C_0402_1005Metric
C18, C23: 10u 16V; C_0805_2012Metric
C20, C21, C25, C26: 22u 10V; C_1206_3216Metric
C22, C27: 3n3; C_0402_1005Metric
C29, C30: 18p; C_0402_1005Metric
C39: 4u7; C_0603_1608Metric
D4: USBLC6-2P6; SOT-666
F1: 1 A (kendini onaran); Fuse_1812_4532Metric
FB1: 2 A ferrit; L_0805_2012Metric
J2: USB Type-C; USB_C_Receptacle_GCT_USB4105-xx-A_16P_TopMnt_Horizontal
L1, L2: 2u2 XAL4020-222; L_Coilcraft_XAL4020-XXX
R12, R13: 5k1; R_0402_1005Metric
R14: 316k 1%; R_0402_1005Metric
R15, R16: 100k 1%; R_0402_1005Metric
R17: 200k 1%; R_0402_1005Metric
R18: 64k9 1%; R_0402_1005Metric
R19: 10k 1%; R_0402_1005Metric
R20, R27, R28, R29, R30: 10k; R_0402_1005Metric
R21: 12k 1%; R_0402_1005Metric
R22: 1k; R_0402_1005Metric
R23, R24, R25, R26: 100k; R_0402_1005Metric
U5, U6: TPS62130RGTR; VQFN-16-1EP_3x3mm_P0.5mm_EP1.68x1.68mm_ThermalVias
U7: TPS3808G01DBVR; SOT-23-6
U8: USB2514Bi-AEZG; QFN-36-1EP_6x6mm_P0.5mm_EP3.7x3.7mm
Y2: 24 MHz; Crystal_SMD_3225-4Pin_3.2x2.5mm

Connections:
+1V2: C25.1, C26.1, L2.2, R16.1, U6.14 (VOS); also elsewhere on the board
+3V3: C20.1, C21.1, C28.1, C33.1, C34.1, C35.1, C36.1, C37.1, C38.1, C39.1, L1.2, R14.1, R18.1, R20.1, R22.1, R23.1, R25.1, R27.1, R28.1, R29.1, R30.1, U5.14 (VOS), U7.6 (VDD), U8.5 (VDDA33), U8.10 (VDDA33), U8.15 (VDD33), U8.23 (VDD33), U8.29 (VDDA33), U8.36 (VDDA33); also elsewhere on the board
+5V: C16.1, C17.1, C18.1, C19.1, C23.1, C24.1, FB1.2, U5.10 (VIN), U5.11 (VIN), U5.12 (VIN), U5.13 (EN), U6.10 (VIN), U6.11 (VIN), U6.12 (VIN), U6.13 (EN); also elsewhere on the board
GND: C16.2, C17.2, C18.2, C19.2, C20.2, C21.2, C22.2, C23.2, C24.2, C25.2, C26.2, C27.2, C28.2, C29.2, C30.2, C31.2, C32.2, C33.2, C34.2, C35.2, C36.2, C37.2, C38.2, C39.2, D4.2 (GND), J2.A1 (GND), J2.A12 (GND), J2.B1 (GND), J2.B12 (GND), J2.SH (SHIELD), R12.2, R13.2, R15.2, R17.2, R19.2, R21.2, R24.2, R26.2, U5.6 (GND), U5.7 (FSW), U5.8 (DEF), U5.15 (GND), U5.16 (GND), U5.17 (GND), U6.6 (GND), U6.7 (FSW), U6.8 (DEF), U6.15 (GND), U6.16 (GND), U6.17 (GND), U7.2 (GND), U8.11 (TEST), U8.37 (VSS), Y2.2 (G), Y2.4 (G); also elsewhere on the board
HUB_CFG0: R24.1, U8.24 (SCL/SMBCLK/CFG_SEL0)
HUB_CFG1: R23.2, U8.25 (HS_IND/CFG_SEL1)
HUB_CRFILT: C31.1, U8.14 (CRFILT)
HUB_DIS3M: R28.2, U8.6 (USBDM_DN3/PRT_DIS_M3)
HUB_DIS3P: R27.2, U8.7 (USBDP_DN3/PRT_DIS_P3)
HUB_DIS4M: R30.2, U8.8 (USBDM_DN4/PRT_DIS_M4)
HUB_DIS4P: R29.2, U8.9 (USBDP_DN4/PRT_DIS_P4)
HUB_NR0: R26.1, U8.28 (SUSP_IND/LOCAL_PWR/NON_REM0)
HUB_NR1: R25.2, U8.22 (SDA/SMBDATA/NON_REM1)
HUB_PLLFILT: C32.1, U8.34 (PLLFILT)
HUB_RBIAS: R21.1, U8.35 (RBIAS)
HUB_VBUS_DET: R22.2, U8.27 (VBUS_DET)
HUB_XI: C29.1, U8.33 (XTALIN/CLKIN), Y2.1
HUB_XO: C30.1, U8.32 (XTALOUT), Y2.3
REG_1V2_FB: R16.2, R17.1, U6.5 (FB)
REG_1V2_SS: C27.1, U6.9 (SS/TR)
REG_1V2_SW: L2.1, U6.1 (SW), U6.2 (SW), U6.3 (SW)
REG_3V3_FB: R14.2, R15.1, U5.5 (FB)
REG_3V3_SS: C22.1, U5.9 (SS/TR)
REG_3V3_SW: L1.1, U5.1 (SW), U5.2 (SW), U5.3 (SW)
RST_SENSE: R18.2, R19.1, U7.5 (SENSE)
USB1_DM: U8.1 (USBDM_DN1/PRT_DIS_M1); also elsewhere on the board
USB1_DP: U8.2 (USBDP_DN1/PRT_DIS_P1); also elsewhere on the board
USB2_DM: U8.3 (USBDM_DN2/PRT_DIS_M2); also elsewhere on the board
USB2_DP: U8.4 (USBDP_DN2/PRT_DIS_P2); also elsewhere on the board
USB_CC1: J2.A5 (CC1), R12.1
USB_CC2: J2.B5 (CC2), R13.1
USB_RESET_N: R20.2, U7.1 (~RESET), U8.26 (RESET_N); also elsewhere on the board
USB_UP_DM: D4.3 (I/O2), D4.4 (I/O2), J2.A7 (D-), J2.B7 (D-), U8.30 (USBDM_UP)
USB_UP_DP: D4.1 (I/O1), D4.6 (I/O1), J2.A6 (D+), J2.B6 (D+), U8.31 (USBDP_UP)
VBUS_F: F1.2, FB1.1
VBUS_USB: D4.5 (VBUS), F1.1, J2.A4 (VBUS), J2.A9 (VBUS), J2.B4 (VBUS), J2.B9 (VBUS)

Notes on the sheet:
USB GOBEGI (USB2514B, 24 MHz): 1. port Ethernet koprusu, 2. port dugum islemcisi; 3. ve 4. portlar 10 k yukari cekmeyle kapali.
BESLEMELER: 5 V -> 3,3 V ve 5 V -> 1,2 V (iki TPS62130). Ethernet koprusunun 1,2 V hatti yaklasik 0,46 A, 3,3 V hatti yaklasik 0,21 A ceker.
SIFIRLAMA: 3,3 V yaklasik 3,0 V'u gecene kadar gobek ve Ethernet koprusu sifirda tutulur.
Kayis uclari: veri yolundan beslenen gobek, 1. ve 2. portlar cikarilamaz aygit (ayar tablosu uretici belgesiyle dogrulanacak).
USB TYPE-C GIRISI: kart USB'den beslenir (yaklasik 2 W). Sigorta + ferrit; VBUS uzerinde buyuk kondansator yok (USB ani akim siniri).

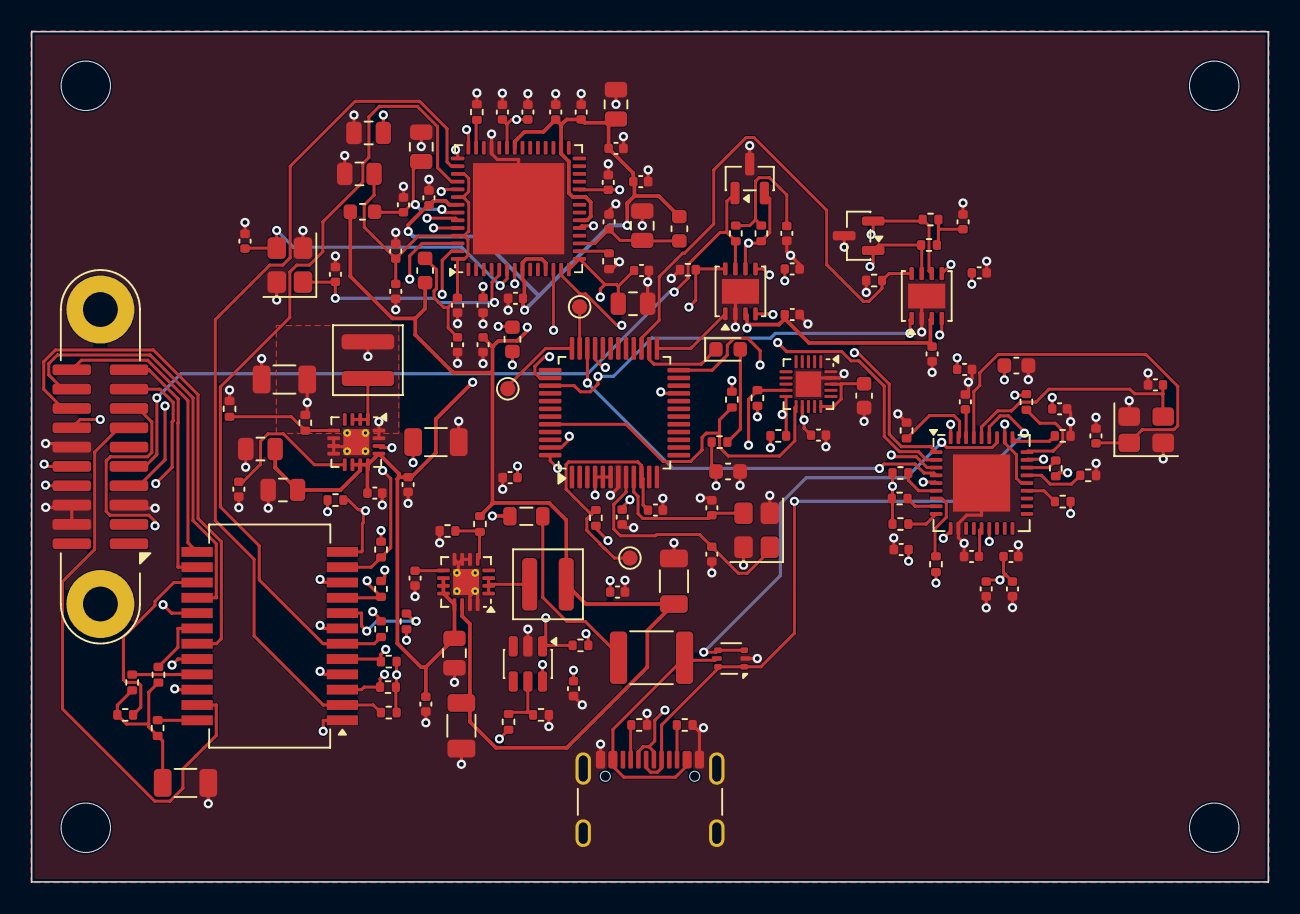
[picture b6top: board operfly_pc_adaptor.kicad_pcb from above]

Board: 4 copper layers, 80.0 x 55.0 mm, 144 parts (0 on the bottom side), 88 nets.

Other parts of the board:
H1, H2, H3, H4: M3; MountingHole_3.2mm_M3

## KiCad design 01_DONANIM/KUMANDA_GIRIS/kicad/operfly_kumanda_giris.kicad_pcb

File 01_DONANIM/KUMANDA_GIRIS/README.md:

# Operfly kumanda giriş kartı

Üç kumandada (Pilot 12, Pilot T, Pilot Pro) ortak kart: çubukları, tekerlekleri, anahtarları ve düğmeleri okur.
Kumandanın gerçek zamanlı işlemcisi ve güvenli elemanı bu karttadır. Ana kartla bağlantı:
`13_DOKUMANTASYON/KUMANDA_ARAYUZU.md`.

## Durum (15 Kasım 2026)

- KiCad projesi: `kicad/operfly_kumanda_giris.kicad_pro`.
  Üretim ve denetim: `python 10_ORTAK_ARACLAR/kicad/denetle.py KUMANDA_GIRIS operfly_kumanda_giris`.
- Şematik tamam, 3 sayfa: işlemci/güvenli eleman/bağlantılar (`islemci`), girişler (`girisler`).
  ERC 0 hata, 0 uyarı. Kart çizimi başlamadı.

## Kararlar (sahibi kararı tasarımcıya bıraktı)

1. **Kumandanın işlemcisi bu kartta.** Malzeme listesinde kumandalarda tek işlemci var ve giriş kartında sayılıyor;
   işlemci hem girişleri okur hem kumanda radyosunu sürer. Kumanda yolu Pilot Pro'daki Jetson'dan bağımsız kalır:
   Jetson kilitlense de araç kumanda edilebilir.
2. **Güvenli eleman (SE050) işlemcinin yanında**, ana kartta değil. Anahtarlar ve şifreleme aynı kartta kalır;
   kartlar arası kabloda anahtarla ilgili hat dolaşmaz.
3. **Omurga düğümü değil.** Kumandanın içinde CAN ve 12 V yok; ortak düğüm devresi yerine yalnızca işlemci, kristal
   ve güvenli eleman kullanıldı. İşlemci aynı (STM32G0B1CET6): yazılım araçları ve kimlik doğrulama kodu ortak.
4. **Ana kart bağlantısı 20 kontaklı yassı kablo:** besleme, kumanda radyosunun seri hatları ve denetimi, USB, I2C,
   güç düğmesi/tutma, sesli uyarıcı. Tanım ayrı belgede; Pilot 12, T ve Pro ana kartları buna uyacak.
5. **Çubuklar analog, oransal ölçüm.** Çubukların beslemesi ve işlemcinin ölçüm referansı aynı süzülmüş raydan
   (+3V3A) gelir; besleme dalgalanması ölçümü etkilemez. Her girişte 1 k + 100 nF.
6. **Anahtarlar tek analog girişle okunur.** İki 47 k orta konumu yarı gerilime çeker; aynı devre 2 ve 3 konumlu
   anahtarı okur, kopuk kablo "orta" göründüğü için arıza yazılımda anlaşılır. Altı anahtar altı giriş kullanır.
7. **12 kanal:** 4 çubuk ekseni + 2 tekerlek + 6 anahtar. Ayrıca 2 düğme ve menü için 5 yönlü tuş (tek analog giriş,
   direnç merdiveni).
8. **Çubuk ve anahtarlar kartta değil, kabloyla bağlanır** (kasaya vidalanan parçalar). Konnektör uç sıraları
   Operfly tanımıdır; satın alınan parçanın kablosu buna göre hazırlanır.
9. **Ekran/genişleme konnektörü** (SPI + denetim hatları): Pilot T'nin küçük ekranı için. Pilot 12'de boş kalır.
10. **USB işlemciden ana karta gider:** ayar, yazılım güncelleme ve (Pilot Pro'da) çubuk verisinin Jetson'a aktarımı.

## Sahibinin bilmesi gerekenler

- **Çubuk (gimbal) modeli seçilmedi.** Baktığım hazır Hall gimbal (RadioMaster AG01) 3,3 V ile çalışıyor; ancak
  ürün sayfalarında konnektör uç sırası ve çıkış gerilim aralığı yok. Kart bu yüzden kendi tanımladığımız
  4 uçlu girişle çizildi; seçilen gimbalin kablosu numune üzerinde ölçülerek uyarlanacak. Çıkışı analog olmayan
  (sayısal) bir gimbal seçilirse bu kart değişir.
- **Anahtar, tekerlek ve düğmeler de seçilmedi** (kasa tasarımıyla birlikte seçilecek).

## Doğrulanacaklar

- Seçilen gimbalin besleme akımı, çıkış aralığı (0-3,3 V içinde mi) ve uç sırası; gerekirse giriş bölücüsü.
- İşlemcinin 29 ve 32 numaralı uçları (BUZZER, LED_DURUM) USB-PD "ölü batarya" işleviyle paylaşımlıdır; açılışta
  bu uçlarda iç aşağı çekme bulunur, yazılım kapatmalıdır. Sesli uyarıcı ve ışık için sakıncası yok, denenecek.
- Analog girişlerin kaynak direnci (anahtarlarda yaklaşık 24 k) ile örnekleme süresi ayarı.
- Kullanıcının dokunduğu parçalardan (çubuk, anahtar gövdesi) gelebilecek statik boşalma: kasa topraklaması ve
  gerekirse giriş koruma diyotları kart çiziminde değerlendirilecek.
- Yassı kablonun kontak yönü ve uzunluğu (USB tam hız hattı taşıyor; kısa tutulacak).
- Ekran (Pilot T): EA DOGM128W-6 seçildi ve bu konnektöre uyuyor (bkz. `01_DONANIM/KUMANDA_T`); MISO ucu kullanılmıyor.
- SE050 ayak izi geçici (düğüm devresiyle ortak not).

## Kart çizimi (otomatik)

Sahibinin kararıyla kart **otomatik** çizildi: yerleşim `pcb_yerlesim.py`, yollar dış bir otomatik yol çiziciyle
(`pcb_ciz.py`). Dosya: `kicad/operfly_kumanda_giris.kicad_pcb`; ayarlar `kicad/pcb_ayar.py`.
Yeniden üretmek için: `python 10_ORTAK_ARACLAR/kicad/pcb_ciz.py KUMANDA_GIRIS operfly_kumanda_giris`.

- **Kart:** 75 x 55 mm, 4 katman (üst: elemanlar + sinyal, iç 1: toprak, iç 2: +3V3, alt: sinyal), 102 eleman, tamamı üst yüzde; köşelerde M3 montaj deliği.
- **Kurallar:** yol 0,20 mm, açıklık 0,125 mm, geçiş 0,6/0,3 mm; besleme ağları, ağın en dar ucunu aşmayacak biçimde 0,2-1,0 mm (0,4 mm ve üstünde geçiş 0,8/0,4 mm); bakır-kenar 0,25 mm.
- **Denetim:** DRC 0 ihlal, 0 bağlanmamış uç; şematik-kart uyumu temiz. 768 yol parçası, 172 geçiş.

**Bu bir mühendis çizimi değildir.** Üretimden önce bir kart tasarımcısının bakması gereken noktalar:

- On beş konnektör kart kenarlarına otomatik dizildi; yerleri kumanda kasasındaki çubuk, anahtar ve düğmelerin konumuna göre seçilmedi (kasa henüz tasarlanmadı).
- Çubuk ölçüm hatları (analog) ve analog besleme (+3V3A) sayısal hatlardan ayrılmadı; çubuk okumalarındaki gürültü ölçülmeli.
- Yassı kablo konnektöründeki USB çifti eşit uzunlukta çizilmedi.
- Anahtarlamalı regülatörlerin (bobin, diyot, giriş/çıkış kondansatörleri) akım döngüleri küçük tutulmadı; gürültü ve verim ölçülmeli.
- Kristal ve osilatör hatları en kısa yoldan çizilmedi; altlarından başka sinyal geçip geçmediğine bakılmalı.
- Fark çiftleri (CAN, USB, Ethernet) çift olarak, eşit uzunlukta ve empedans denetimli çizilmedi.
- Güç elemanlarının soğutma bakırı ve ısıl geçişleri ayrıca hesaplanmadı.
- Eleman adları üretim katmanında bırakıldı; kart üstünde yazı (serigrafi) yok.
- Kasa, konnektör yerleri ve montaj delikleri mekanik tasarımla eşleştirilmedi.
- Üretim dosyaları (Gerber, delik, dizgi) henüz çıkarılmadı.

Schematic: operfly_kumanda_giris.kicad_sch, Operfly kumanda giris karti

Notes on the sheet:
Operfly kumanda giris karti (Pilot 12, Pilot T ve Pilot Pro'da ortak)
Sematik betikle uretilir: 01_DONANIM/KUMANDA_GIRIS/kicad/uret.py.

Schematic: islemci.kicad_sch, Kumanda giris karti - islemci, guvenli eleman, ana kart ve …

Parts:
C1, C7: 4u7; C_0603_1608Metric
C2, C3, C6, C9, C10: 100n; C_0402_1005Metric
C4, C5: 10p; C_0402_1005Metric
C8: 1u; C_0402_1005Metric
C11: 2u2; C_0603_1608Metric
C12: 10u; C_0805_2012Metric
D1: LED yesil; LED_0603_1608Metric
D2: LED kirmizi; LED_0603_1608Metric
FB1: BLM18PG221; L_0603_1608Metric
J1: Ana kart (FFC 20); Hirose_FH12-20S-0.5SH_1x20-1MP_P0.50mm_Horizontal
J2: Ekran / genisleme; JST_GH_SM10B-GHS-TB_1x10-1MP_P1.25mm_Horizontal
R1, R6, R8, R9, R13: 10k; R_0402_1005Metric
R2, R3: 1k; R_0402_1005Metric
R4, R5: 2k2; R_0402_1005Metric
R7, R10, R11, R12, R14: 100k; R_0402_1005Metric
TP1: SWDIO; TestPoint_Pad_D1.0mm
TP2: SWCLK; TestPoint_Pad_D1.0mm
TP3: NRST; TestPoint_Pad_D1.0mm
U1: STM32G0B1CET6; LQFP-48_7x7mm_P0.5mm
U2: SE050E2HQ1; QFN-20-1EP_3x3mm_P0.4mm_EP1.65x1.65mm
Y1: 16 MHz; Crystal_SMD_3225-4Pin_3.2x2.5mm

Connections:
+3V3: C1.1, C2.1, C3.1, C10.1, C12.1, FB1.1, J1.2, J1.3, J2.1, R1.1, R2.1, R3.1, R4.1, R5.1, R6.1, R8.1, R9.1, R10.1, R13.1, U1.4 (VBAT), U1.6 (VDD), U2.12 (VIN); also elsewhere on the board
+3V3A: C7.1, C8.1, C9.1, FB1.2, U1.5 (VREF+); also elsewhere on the board
ALERT_N: J1.17, R9.2, U1.1 (PC13)
BTN_1: U1.2 (PC14); also elsewhere on the board
BTN_2: U1.3 (PC15); also elsewhere on the board
BUZZER: J1.20, R12.1, U1.29 (PA9/UCPD1_DBCC1)
DISP_BL: J2.9, R14.1, U1.28 (PA8)
DISP_CS: J2.6, R13.2, U1.37 (PA15)
DISP_DC: J2.7, U1.30 (PC6)
DISP_MISO: J2.5, U1.26 (PB14)
DISP_MOSI: J2.4, U1.27 (PB15)
DISP_RST: J2.8, U1.31 (PC7)
DISP_SCK: J2.3, U1.25 (PB13)
GIM_L_X: U1.11 (PA0); also elsewhere on the board
GIM_L_Y: U1.12 (PA1); also elsewhere on the board
GIM_R_X: U1.13 (PA2); also elsewhere on the board
GIM_R_Y: U1.14 (PA3); also elsewhere on the board
GND: C1.2, C2.2, C3.2, C4.2, C5.2, C6.2, C7.2, C8.2, C9.2, C10.2, C11.2, C12.2, J1.1, J1.4, J1.11, J1.14, J1.MP (MountPin), J2.2, J2.10, J2.MP (MountPin), R7.2, R11.2, R12.2, R14.2, U1.7 (VSS), U2.19 (VSS), U2.21 (EP), Y1.2 (G), Y1.4 (G); also elsewhere on the board
HSE_IN: C4.1, U1.8 (PF0), Y1.1
HSE_OUT: C5.1, U1.9 (PF1), Y1.3
I2C_SCL: J1.15, R4.2, U1.47 (PB8), U2.10 (I2C_SCL)
I2C_SDA: J1.16, R5.2, U1.48 (PB9), U2.9 (I2C_SDA)
LED_DURUM: D1.1 (K), U1.32 (PA10/UCPD1_DBCC2)
LED_DURUM_A: D1.2 (A), R2.2
LED_UYARI: D2.1 (K), U1.24 (PB12)
LED_UYARI_A: D2.2 (A), R3.2
NAV_ADC: U1.23 (PB11); also elsewhere on the board
NRST: C6.1, R1.2, TP3.1, U1.10 (PF2)
PWR_BTN_N: J1.18, R10.2, U1.41 (PD3)
PWR_HOLD: J1.19, R11.1, U1.40 (PD2)
RADIO_BOOT_N: J1.10, R8.2, U1.39 (PD1)
RADIO_CTS: J1.7, U1.42 (PB3)
RADIO_OFF: J1.9, R7.1, U1.38 (PD0)
RADIO_RTS: J1.8, U1.43 (PB4)
RADIO_RXD: J1.5, U1.45 (PB6)
RADIO_TXD: J1.6, U1.46 (PB7)
SE_ENA: R6.2, U1.44 (PB5), U2.11 (ENA)
SE_VCC: C11.1, U2.15 (VOUT), U2.18 (VCC)
SWCLK: TP2.1, U1.36 (PA14)
SWDIO: TP1.1, U1.35 (PA13)
SW_A: U1.17 (PA6); also elsewhere on the board
SW_B: U1.18 (PA7); also elsewhere on the board
SW_C: U1.19 (PB0); also elsewhere on the board
SW_D: U1.20 (PB1); also elsewhere on the board
SW_E: U1.21 (PB2); also elsewhere on the board
SW_F: U1.22 (PB10); also elsewhere on the board
USB_DM: J1.12, U1.33 (PA9/PA11)
USB_DP: J1.13, U1.34 (PA10/PA12)
WHEEL_L: U1.15 (PA4); also elsewhere on the board
WHEEL_R: U1.16 (PA5); also elsewhere on the board

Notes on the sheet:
GUVENLI ELEMAN (SE050): kumandanin kimligi ve anahtarlari islemcinin yaninda durur. I2C yukari cekmeleri bu karttadir.
ISLEMCI (STM32G0B1CET6): cubuklari ve anahtarlari okur, kumanda paketini sifreler, kumanda radyosunu dogrudan surer.
Boylece kumanda yolu, ust modeldeki Jetson'a ya da ekrana bagli degildir. 14 analog giristen 13'u kullanilir.
EKRAN / GENISLEME (10 kontak): Pilot T'nin kucuk ekrani icin SPI + denetim hatlari. Pilot 12'de bos kalir.
ANA KART BAGLANTISI (20 kontakli yassi kablo, 0,5 mm): besleme ana karttan gelir. Uc sirasi: 13_DOKUMANTASYON/KUMANDA_ARAYUZU.md.
Radyo hatlari ana karttaki kumanda radyosuna, USB ana karttaki Type-C konnektore, I2C batarya olcere gider.
olcum oransal oldugu icin besleme dalgalanmasi sonucu etkilemez.
ANALOG BESLEME (+3V3A): ferrit + kondansator. Islemcinin olcum referansi ve cubuklarin beslemesi ayni raydadir;
